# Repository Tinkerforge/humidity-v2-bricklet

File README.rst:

Humidity Bricklet 2.0
=====================

This repository contains the firmware source code and the hardware design
files. The documentation generator configs can be found at
https://github.com/Tinkerforge/generators

Repository Content
------------------

software/:
 * examples/: Examples for all supported languages
 * build/: Compiled files
 * src/: Source code of firmware
 * Makefile: Makefile to build project

hardware/:
 * Contains KiCad project files and additionally schematics as PDF

datasheets/:
 * Contains datasheets for sensors and complex ICs that are used

Hardware
--------

The hardware is designed with the open source EDA Suite KiCad
(http://www.kicad.org). Before you are able to open the files,
you have to install the Tinkerforge kicad-libraries
(https://github.com/Tinkerforge/kicad-libraries). You can either clone
them directly in hardware/ or clone them in a separate folder and
symlink them into hardware/
(ln -s kicad_path/kicad-libraries project_path/hardware). After that you
can open the .pro file in hardware/ with KiCad and from there view and
modify the schematics and the PCB layout.

Software
--------

If you want to do your own Brick/Bricklet firmware development we highly
recommend that you use our build environment setup script and read the
tutorial (https://www.tinkerforge.com/en/doc/Tutorials/Tutorial_Build_Environment/Tutorial.html).

To compile the C code we recommend you to install the newest GNU Arm Embedded
Toolchain (https://launchpad.net/gcc-arm-embedded/+download).
You also need to install bricklib2 (https://github.com/Tinkerforge/bricklib2).

You can either clone it directly in software/src/ or clone it in a
separate folder and symlink it into software/src/
(ln -s bricklib_path/bricklib2 project_path/software/src/). Finally make sure to
have CMake installed (http://www.cmake.org/cmake/resources/software.html).

After that you can build the firmware by invoking make in software/.
The firmware (.zbin) can then be found in software/build/ and uploaded
with brickv (click button "Flashing" on start screen).

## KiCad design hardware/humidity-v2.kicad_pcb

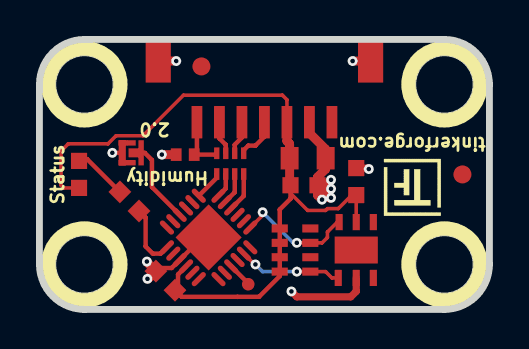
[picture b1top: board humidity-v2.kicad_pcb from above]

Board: 2 copper layers, 25.0 x 15.0 mm, 21 parts (1 on the bottom side), 16 nets.

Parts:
C101: 10uF; C0805
C102: 220pF; C0402F
C103: 1uF; C0603F
C104, C105: 100nF; C0603F
D101: blue; D0603F
Fiducial_Mark: VAL**; Fiducial_Mark
Fiducial_Mark#2: VAL**; Fiducial_Mark
P101: CON-SENSOR2
P102: DEBUG; DEBUG_PAD
P103: BOOT; SolderJumper
R101: 1k; R0603F
RP101: 82; 4X0402
RP102: 4k7; 0603X4
U101: XMC1100-16; QFN24-4x4mm-0.5mm
U102: HDC1080; DFN6-30x30_humidity
U103, U104, U105, U106: DRILL; DRILL_NP
VAL: CE_5mm

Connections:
GND: C101.1, C102.1, C103.1, C104.2, C105.2, P101.2, P101.EP, P103.1, U101.9, U101.EXP, U102.2
unnamed: C102.2, P101.7, RP101.4
unnamed: D101.2, R101.2
unnamed: P101.4, RP101.1
unnamed: P101.5, RP101.2
unnamed: P101.6, RP101.3
unnamed: P102.1, U101.15
unnamed: P103.2, U101.4
unnamed: R101.1, U101.7
S-CLK: RP101.7, U101.23
S-CS: RP101.8, U101.22
S-MISO: RP101.5, U101.1
S-MOSI: RP101.6, U101.24
SCL: RP102.7, U101.19, U102.6
SDA: RP102.5, U101.17, U102.1
VCC: C101.2, C103.2, C104.1, C105.1, D101.1, P101.3, RP102.1, RP102.2, RP102.3, RP102.4, U101.10, U102.5

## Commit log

2017-05-24 Add initial stub implementation of Humidiy Bricklet 2.0
2017-05-24 Add callback value type configuration
2017-05-24 Remove unnecessary comment
    The address at that point is used for i2c slave, but we are i2c master.
2017-05-29 Add gitignore
2017-05-29 Use 100khz baudrate, it is more then fast enough
2017-05-29 Add moving average for humidity/temperature values
2017-05-30 Remove debug
2017-07-11 adding hardware files
2017-08-01 Add 3d information (tbc)
2017-08-03 Add 3d information (final)
2017-08-03 Add 3d model (*.step & *.FCStd)
2017-08-11 define filter circuit
2017-09-19 specify processor
2017-11-06 Add final schematic
2017-11-17 Add simple examples
2017-11-21 Remove WIP marker
2017-11-21 Rename file
2017-11-24 Add more examples
2017-11-24 Fix typos in examples
2017-11-24 Fix more typos in examples
2017-12-07 mathematica: Also generate .nb files
2018-01-30 Update examples
2018-02-19 javascript: Close div tag correctly
2018-02-20 Cleanup KiCad libraries config
    Ensure LibDir=kicad-libraries and LibName1=tinkerforge.
    Remove special library.
2018-03-05 Remove unused flash-size define
2018-03-27 Add LabVIEW examples
2018-03-27 labview: Fix typo in comment
2018-05-11 Rename files
2018-05-24 perl: Use strict in examples
2018-06-06 fix coordinate origin
2018-06-06 Remove dummy calls
2018-06-06 Adapt to bricklib2 callback-value changes to fix wrong length of get-humidity and get-temperature packets
2018-06-06 Update changelog and version
2018-06-07 Add date ref for version 2.0.1 to changelog
2018-06-18 Change capacitor footprint(s) to C0402F
2018-06-27 Fix "Status" marking
2018-06-28 Fix readme
2018-07-11 Add Makefile with docker support
2018-07-11 Remove obsolete generate_makefile scripts
2018-07-11 Update directory structure and build instructions
2018-07-18 examples: Fix typo
2018-10-04 Increase version for new release (changes in bricklib2)
2018-10-04 Add rev to changelog
2018-10-15 Add SetSamplesPerSecond configuration function
2018-10-15 Add 2.0.3 rev to changelog
2018-11-06 Add rust examples
2018-11-07 rust: Accept host names for ip connection, fix naming inconsistencies
2018-11-07 rust: Rename callback receivers.
2018-12-14 Add go examples.
2018-12-14 go: Fix printf parameters.
2018-12-18 go: Change import path.
2018-12-18 go: Change import path again.
2018-12-20 rust: Reformat examples.
2019-01-18 update project settings
2019-01-24 mqtt: Add examples.
2019-01-24 mqtt: Fix example header.
2019-01-24 mqtt: Remove executable bit in example permissions.
2019-01-24 go: Minor example fixes.
2019-01-24 mqtt: Minor example fixes.
2019-03-28 mqtt: Fix whitespace.
2019-04-04 Fix bug in GetSamplesPerSecond (was not returning the value)
2019-04-05 added humidity 2.1 with thermal cutouts
2019-04-05 new inverted slot design
2019-04-05 new 25x25 design
2019-04-08 Fix bug in GetSamplesPerSecond (packet length not set)
2019-08-22 c: Adapt to bindings changes
2019-08-27 go: Escape '%' in examples.
2020-01-13 examples: Use python3 input instead of python2 raw_input.
2020-01-13 examples: mqtt: Remove trailing whitespace.
2020-08-19 Add uc examples.
2020-08-25 uc: Fix whitespace
2020-08-27 uc: Fix warnings.
2020-09-02 uc: Add example driver note.
2020-10-16 uc: Fix divisor type.
2021-10-25 Update KiCad link
    https://www.kicad.org/blog/2021/10/Avoid-links-to-former-kicad-domain/
2022-04-19 examples: uc: Rename TF_HalContext to TF_HAL.
2022-04-27 uc: Adapt to bindings changes
2022-07-06 Add license files.
2023-01-27 fix schamtic
2023-01-27 add schematic
2023-01-27 Data Cleanup
2023-05-22 labview: Add examples that read temperature as well
2025-10-04 Fix compatibility with new Docker build image (GCC 14.2.1)
2026-05-19 update to new kicad version

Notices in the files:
hardware/humidity-v2.kicad_pcb:
Licensed under CERN OHL v.1.1
Copyright (©) 2023, B.Nordmeyer
Copyright Tinkerforge GmbH 2023.
This documentation describes Open Hardware and is licensed under the
CERN OHL v. 1.1.
